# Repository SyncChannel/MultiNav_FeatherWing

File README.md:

# MultiNav_FeatherWing

U-Blox GPS + 9DOF FeatherWing for Adafruit Feather.

Check out my blog post for a full description of this board:

http://syncchannel.blogspot.com/2016/01/multinav-featherwing-for-adafruit.html

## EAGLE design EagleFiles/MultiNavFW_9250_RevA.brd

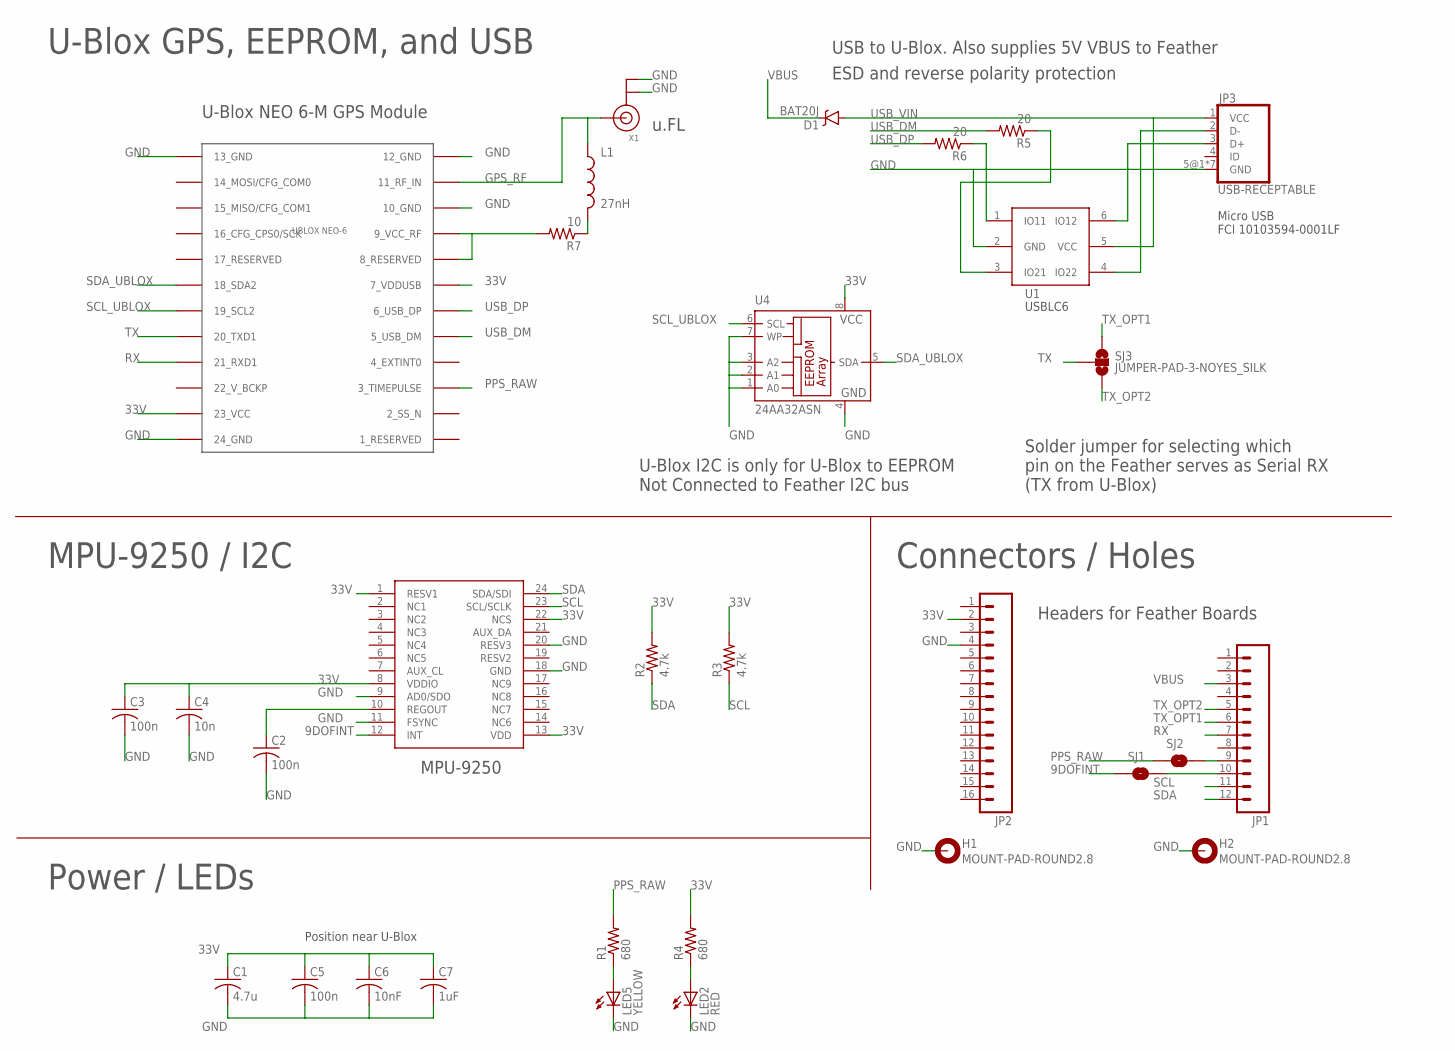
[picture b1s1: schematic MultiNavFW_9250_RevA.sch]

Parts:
C1: 4.7u; C0603
C2, C3, C5: 100n; C0603
C4: 10n; C0603
C6: 10nF; C0603
C7: 1uF; C0603
D1: BAT20J; SOD-323
H1, H2: MOUNT-PAD-ROUND2.8; 2,8-PAD
JP1: M12NO_SILK; 1X12_NO_SILK
JP2: M161X16_NO_SILK; 1X16_NO_SILK
JP3: USB-RECEPTABLE; FCI-10103594-0001LF
L1: 27nH; C0402
LED2: RED; CHIPLED_0603
LED5: YELLOW; CHIPLED_0603
R1, R4: 680; R0603
R2, R3: 4.7k; R0603
R5, R6: 20; R0603
R7: 10; R0603
SJ1, SJ2: SOLDERJUMPERNO; SJ_2S-NO
SJ3: JUMPER-PAD-3-NOYES_SILK; PAD-JUMPER-3-NO_YES_SILK
U1: USBLC6-2; SOT23-6
U2: MPU-9250; LEAD-QFN24
U3: UBLOX_NEO-6; UBLOX_NEO-6P
U4: 24AA32ASN; SO-08
X1: ANTENNA_U.FL; U.FL

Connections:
9DOFINT: SJ1.1, U2.12 (INT)
33V: C1.1, C3.1, C4.1, C5.1, C6.1, C7.1, JP2.2, R2.2, R3.2, R4.2, U2.1 (RESV1), U2.8 (VDDIO), U2.13 (VDD), U2.22 (NCS), U3.7_VDDUSB, U3.23_VCC, U4.8 (VCC)
GND: C1.2, C2.2, C3.2, C4.2, C5.2, C6.2, C7.2, H1.B2,8, H2.B2,8, JP2.4, JP3.5@1 (GND), JP3.5@2 (GND), JP3.5@3 (GND), JP3.5@4 (GND), JP3.5@5 (GND), JP3.5@6 (GND), JP3.5@7 (GND), LED2.C, LED5.C, U1.2 (GND), U2.9 (AD0/SDO), U2.11 (FSYNC), U2.18 (GND), U2.20 (RESV3), U3.10_GND, U3.12_GND, U3.13_GND, U3.24_GND, U4.1 (A0), U4.2 (A1), U4.3 (A2), U4.4 (GND), U4.7 (WP), X1.1 (GND), X1.2 (GND)
GPS_BIAS: R7.2, U3.8_RESERVED, U3.9_VCC_RF
GPS_RF: L1.1, U3.11_RF_IN, X1.3 (SIGNAL)
unnamed: L1.2, R7.1
unnamed: JP3.2 (D-), U1.4 (IO22)
unnamed: R5.1, U1.3 (IO21)
unnamed: R6.1, U1.1 (IO11)
unnamed: LED5.A, R1.1
unnamed: JP3.3 (D+), U1.6 (IO12)
unnamed: LED2.A, R4.1
unnamed: JP1.10, SJ1.2
unnamed: JP1.9, SJ2.2
unnamed: C2.1, U2.10 (REGOUT)
PPS_RAW: R1.2, SJ2.1, U3.3_TIMEPULSE
RX: JP1.7, U3.21_RXD1
SCL: JP1.11, R3.1, U2.23 (SCL/SCLK)
SCL_UBLOX: U3.19_SCL2, U4.6 (SCL)
SDA: JP1.12, R2.1, U2.24 (SDA/SDI)
SDA_UBLOX: U3.18_SDA2, U4.5 (SDA)
TX: SJ3.2, U3.20_TXD1
TX_OPT1: JP1.6, SJ3.1
TX_OPT2: JP1.5, SJ3.3
USB_DM: R5.2, U3.5_USB_DM
USB_DP: R6.2, U3.6_USB_DP
USB_VIN: D1.A, JP3.1 (VCC), U1.5 (VCC)
VBUS: D1.C, JP1.3

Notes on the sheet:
Headers for Feather Boards
Micro USB FCI 10103594-0001LF
U-Blox NEO 6-M GPS Module
U-Blox I2C is only for U-Blox to EEPROM Not Connected to Feather I2C bus
Solder jumper for selecting which pin on the Feather serves as Serial RX (TX from U-Blox)
ESD and reverse polarity protection
u.FL
USB to U-Blox. Also supplies 5V VBUS to Feather
MPU-9250
U-Blox GPS, EEPROM, and USB
Connectors / Holes
MPU-9250 / I2C
Power / LEDs
Position near U-Blox
USBLC6

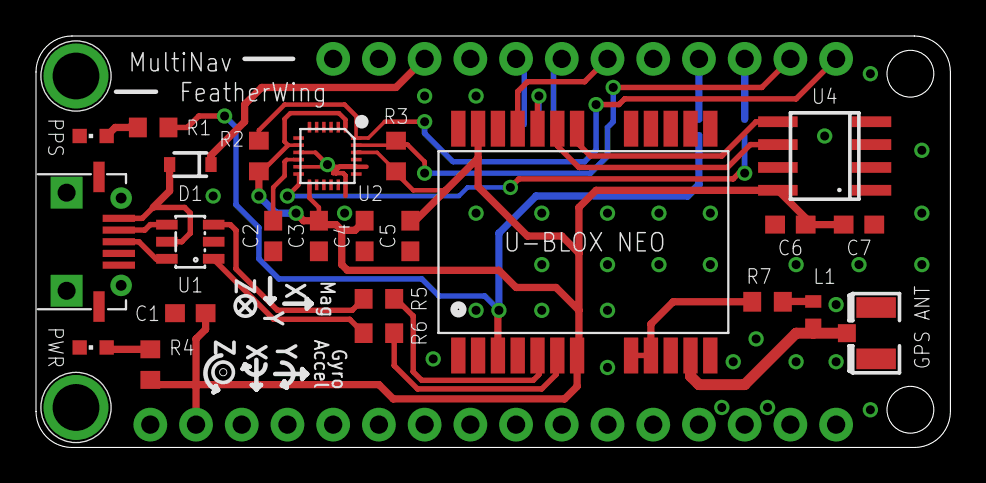
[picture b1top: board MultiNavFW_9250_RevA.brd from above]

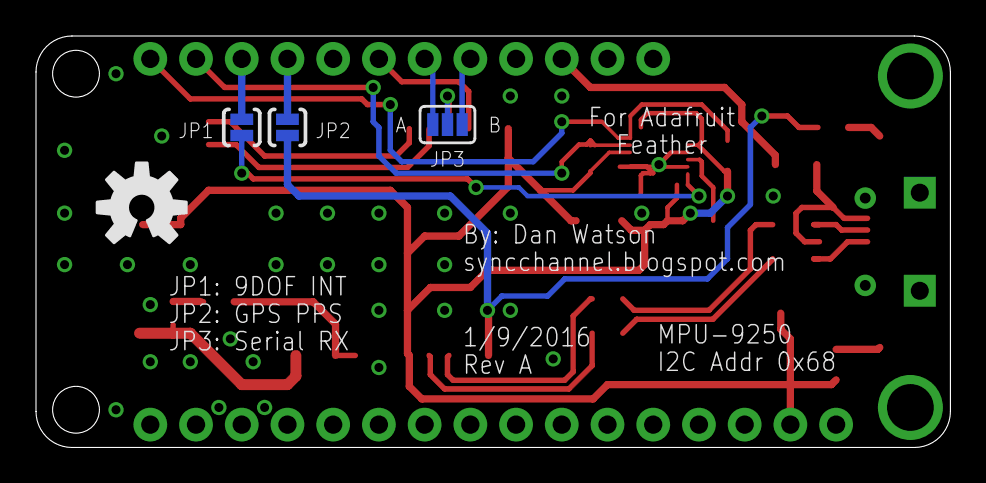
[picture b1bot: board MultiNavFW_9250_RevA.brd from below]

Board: 2 copper layers, 50.8 x 22.9 mm, 32 parts (4 on the bottom side), 28 nets.

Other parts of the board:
U$1: OSHW-LOGO-M

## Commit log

2016-04-26 :space_invader: Added .gitattributes & .gitignore files
2016-04-26 Added Eagle files
2016-05-02 Update Eagle files

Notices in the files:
parts and their libraries:
SparkFun-DiscreteSemi: Licensing: Creative Commons ShareAlike 4.0 International - https://creativecommons.org/licenses/by-sa/4.0
